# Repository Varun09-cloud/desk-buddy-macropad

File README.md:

# Desktop Buddy Macropad 🎛️

Desktop Buddy Macropad is a compact **3-key macropad** with a **rotary encoder**, designed to make everyday computer tasks faster and more convenient. Each key launches a specific application, while the rotary dial provides smooth system volume control.

This project is being built as part of the **Hackpad YSWS**, with a focus on simplicity, usability, and learning the fundamentals of PCB and case design.

---

## ✨ Features

- **3 Mechanical Keys**  
  Each key is mapped to open a specific application (for example: browser, music app, or code editor).

- **Rotary Encoder (EC11)**  
  - Rotate: Volume up / down  
  - Press: Mute  

- **Minimal Desktop Design**  
  No display or unnecessary complexity — focused on reliability and fast input.

- **QMK Firmware**  
  Fully programmable key behavior and encoder actions.

---

## 🎯 Project Goals

- Build a **minimal and functional macropad**
- Learn **PCB design using KiCad**
- Learn **basic case design using Fusion 360**
- Create a Hackpad that is **easy to assemble and customize**

---

## 🧩 Hardware Overview

- **Microcontroller:** Seeed XIAO RP2040  
- **Switches:** MX-style mechanical switches (3×)  
- **Encoder:** EC11 Rotary Encoder  
- **LEDs:** Optional WS2812B RGB LEDs (for underglow or status indication)

---

## 🧱 Case Design

The case will be designed in **Fusion 360** and **3D printed**.

- Compact footprint for desk use  
- Designed to securely hold the PCB  
- Fastened using **M3 screws and heat-set inserts**

---

## 🖥️ PCB Design

- Designed in **KiCad**
- Custom PCB including:
  - 3 MX switch footprints  
  - 1 rotary encoder footprint  
  - XIAO RP2040 footprint  
- PCB size kept under **100 mm × 100 mm** for cost efficiency
- 

---

## 💾 Firmware

Desktop Buddy Macropad uses **KMK firmware** running on **CircuitPython** for the **Seeed XIAO RP2040**.

KMK was chosen because it:
- Runs directly in **Python**
- Is easy to modify and understand
- Works well with rotary encoders and small macropads
- Does not require a complex build environment like QMK

The firmware source code is located in the `/Firmware` folder.

---

### ⚙️ Firmware Features

- **3 mechanical keys**
  - Each key is mapped to a macro or application shortcut
- **Rotary encoder (EC11)**
  - Rotate: Volume up / Volume down
  - Press: Mute
- Easily customizable by editing `main.py`

---

### 📂 Firmware Structure

```text
/Firmware
 ├── main.py        # KMK firmware entry point
 └── lib/           # KMK + CircuitPython libraries

---

## 📦 Bill of Materials (BOM)

| Quantity | Item |
|--------|------|
| 3× | MX Mechanical Switches |
| 3× | DSA Keycaps |
| 2× | 1N4148 DO-35 Diodes |
| 1× | EC11 Rotary Encoder |
| 1× | Seeed XIAO RP2040 |
| — | 3D printed case |
| — | M3 screws + heat-set inserts |

---

## 📂 Repository Structure

```text
/pcb        → KiCad schematic & PCB files
/case       → Fusion 360 CAD files
/firmware   → QMK firmware
/images     → Renders and progress images

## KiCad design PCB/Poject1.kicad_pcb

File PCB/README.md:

# PCB

PCB design files (KiCad project, Gerber outputs, board layouts) for desk-buddy-macropad.

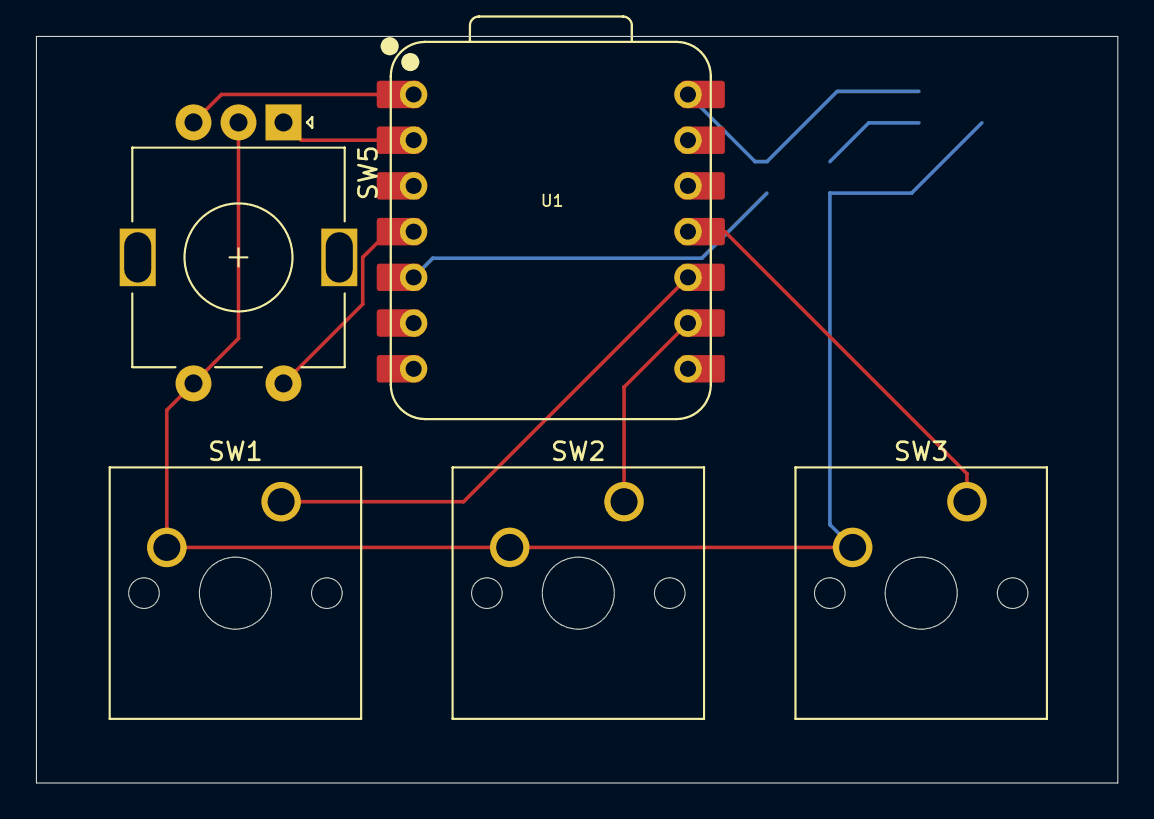
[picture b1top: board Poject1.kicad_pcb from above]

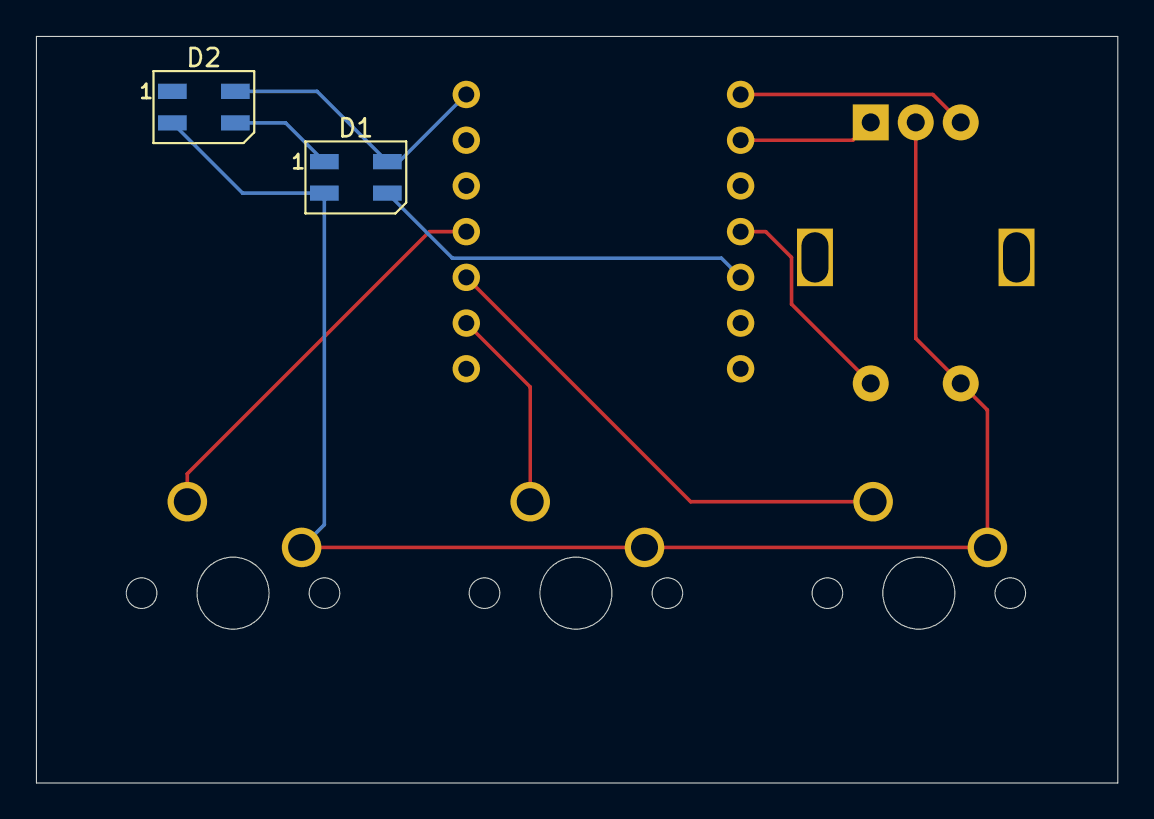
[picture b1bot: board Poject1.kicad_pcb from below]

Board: 2 copper layers, 60.1 x 41.5 mm, 7 parts (2 on the bottom side), 10 nets.

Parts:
D1, D2: SK6812MINI; LED_SK6812MINI_PLCC4_3.5x3.5mm_P1.75mm
SW1, SW2, SW3: SW_Push; SW_Cherry_MX_1.00u_PCB
SW5: RotaryEncoder_Switch; RotaryEncoder_Alps_EC11E-Switch_Vertical_H20mm
U1: XIAO-RP2040-DIP

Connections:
+5V: D1.4 (VDD), D2.4 (VDD), U1.14 (VBUS)
GND: D1.2 (VSS), D2.2 (VSS), SW1.2, SW2.2, SW3.2, SW5.C, SW5.S1
unnamed: D1.3 (DIN), U1.5 (GPIO6/SDA)
unnamed: D1.1 (DOUT), D2.3 (DIN)
unnamed: SW2.1, U1.9 (GPIO2/SCK)
unnamed: SW3.1, U1.11 (GPIO3/MOSI)
unnamed: SW1.1, U1.10 (GPIO4/MISO)
unnamed: SW5.B, U1.1 (GPIO26/ADC0/A0)
unnamed: SW5.A, U1.2 (GPIO27/ADC1/A1)
unnamed: SW5.S2, U1.4 (GPIO29/ADC3/A3)

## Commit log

2026-01-12 Revise README for Desk Buddy Macropad
    Updated project description and features for clarity.
2026-01-12 Add files via upload
    progress images,
2026-01-12 Add files via upload
    PCB file
2026-01-13 Revise README.md for Desktop Buddy Macropad
    Expanded project details, features, goals, hardware overview, case design, PCB design, firmware overview, bill of materials, and repository structure.
2026-01-13 Create PCB
2026-01-13 Create README.md for Desktop Buddy Macropad
    Added detailed project information for Desktop Buddy Macropad.
2026-01-13 Create CAD, PCB and Firmware folders with READMEs
2026-01-13 Restore CAD folder with README
2026-01-13 Add pictures folder with README
2026-01-13 Include CAD, PCB schematics images in README
    Added images of CAD, PCB, and schematic to README.
2026-01-13 Fix image paths in README.md
    Updated image paths in README for PCB and schematic.
2026-01-13 Remove image references from README.md
    Removed images from README.md to streamline content.
2026-01-14 Revise firmware overview and features in README
    Updated firmware section to reflect KMK firmware usage and added features and structure details.
2026-01-14 Update quantity of 1N4148 diodes in README
2026-01-14 Add images to README for case and PCB design
    Added images for the Desktop Buddy case and PCB design.
